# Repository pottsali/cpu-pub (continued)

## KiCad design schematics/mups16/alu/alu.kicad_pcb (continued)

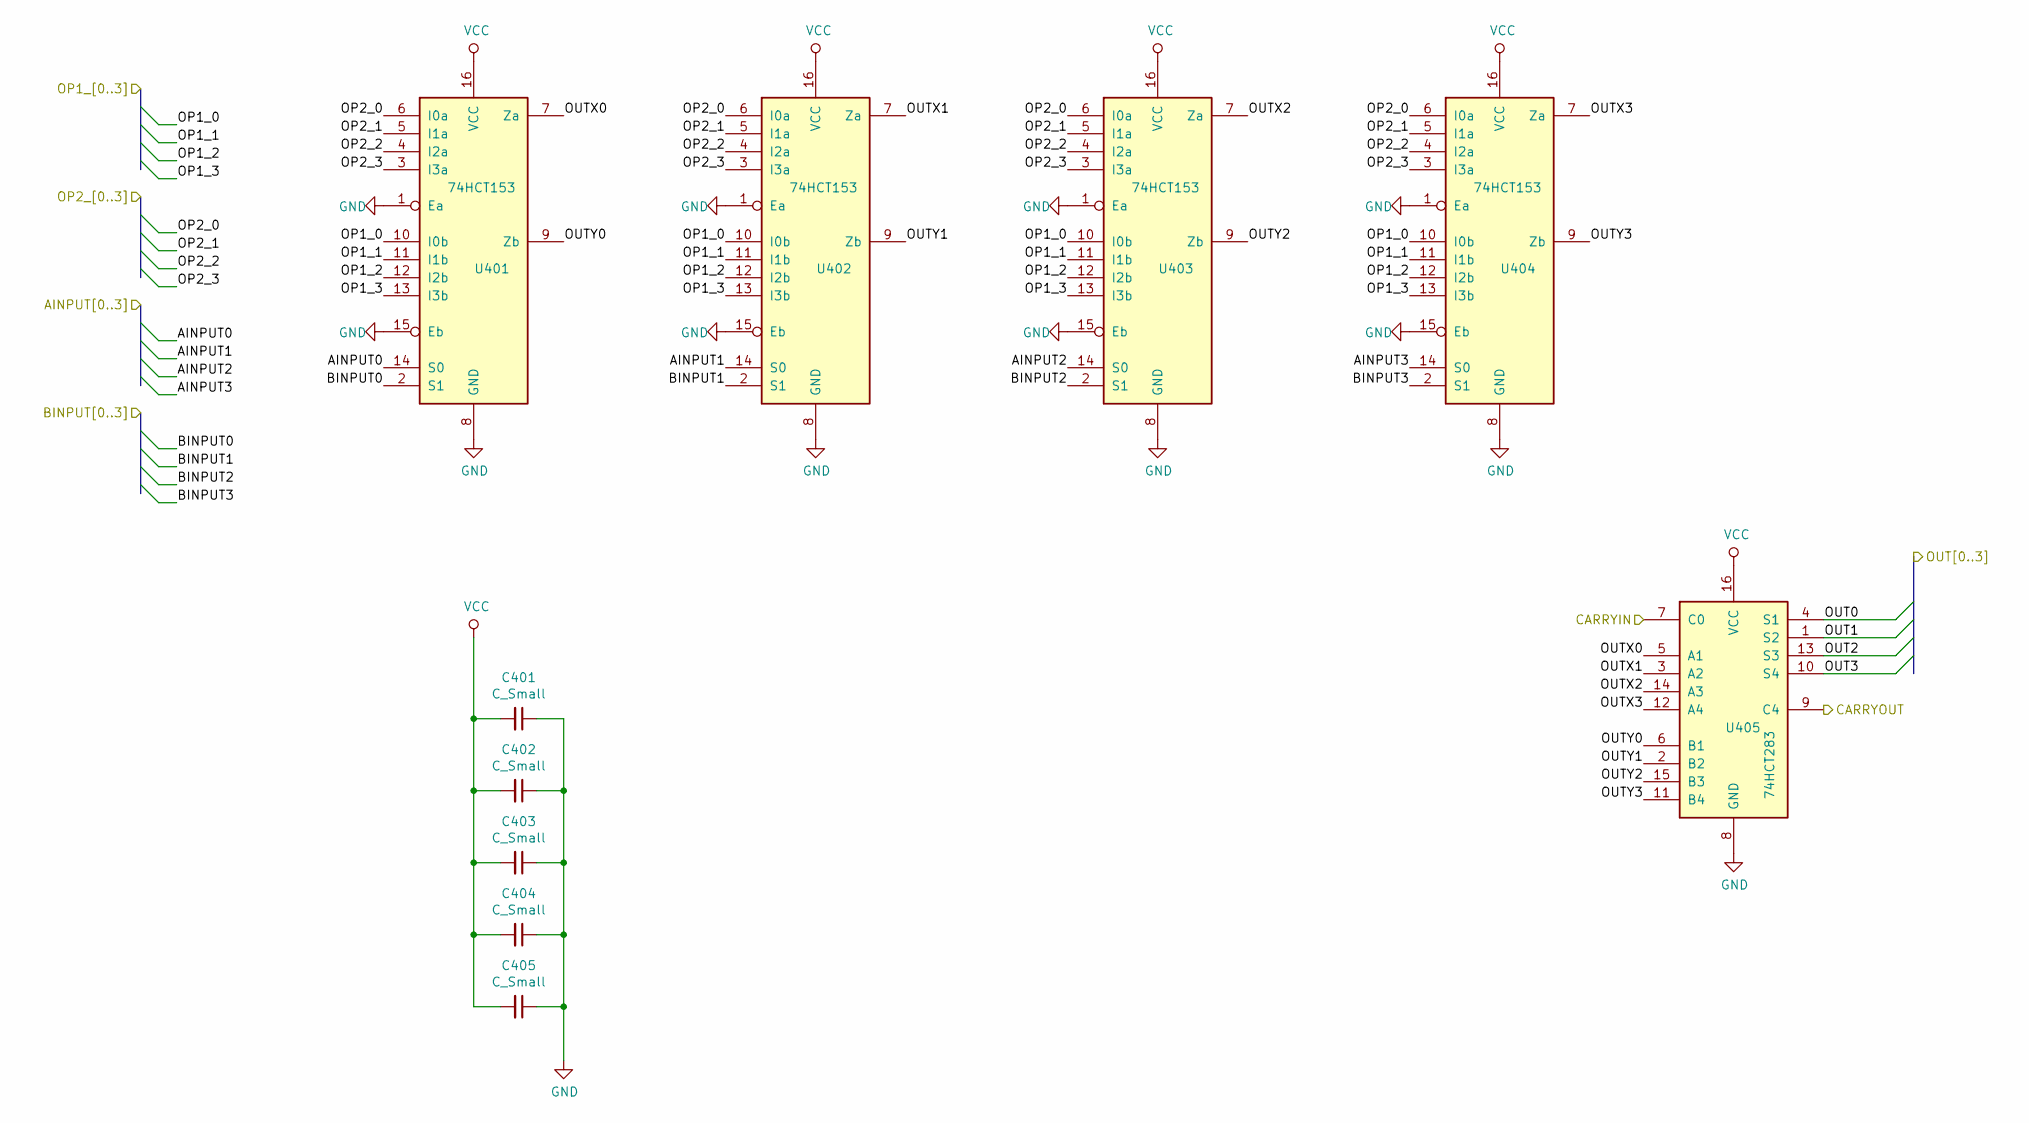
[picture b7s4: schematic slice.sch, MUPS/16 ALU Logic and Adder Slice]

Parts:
C401, C402, C403, C404, C405: C_Small; C_0805_2012Metric
U401, U402, U403, U404: 74HCT153; SOIC-16_3.9x9.9mm_P1.27mm
U405: 74HCT283; SOIC-16_3.9x9.9mm_P1.27mm

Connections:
/ADDOUT0: U405.4 (S1); also elsewhere on the board
/ADDOUT1: U405.1 (S2); also elsewhere on the board
/ADDOUT2: U405.13 (S3); also elsewhere on the board
/ADDOUT3: U405.10 (S4); also elsewhere on the board
/CARRYIN: U405.7 (C0); also elsewhere on the board
/OP_Y0: U401.10 (I0b), U402.10 (I0b), U403.10 (I0b), U404.10 (I0b); also elsewhere on the board
/OP_Y1: U401.11 (I1b), U402.11 (I1b), U403.11 (I1b), U404.11 (I1b); also elsewhere on the board
/OP_Y2: U401.12 (I2b), U402.12 (I2b), U403.12 (I2b), U404.12 (I2b); also elsewhere on the board
/OP_Y3: U401.13 (I3b), U402.13 (I3b), U403.13 (I3b), U404.13 (I3b); also elsewhere on the board
/slice0/OUTX0: U401.7 (Za), U405.5 (A1)
/slice0/OUTX1: U402.7 (Za), U405.3 (A2)
/slice0/OUTX2: U403.7 (Za), U405.14 (A3)
/slice0/OUTX3: U404.7 (Za), U405.12 (A4)
/slice0/OUTY0: U401.9 (Zb), U405.6 (B1)
/slice0/OUTY1: U402.9 (Zb), U405.2 (B2)
/slice0/OUTY2: U403.9 (Zb), U405.15 (B3)
/slice0/OUTY3: U404.9 (Zb), U405.11 (B4)
/slice1/CARRYIN: U405.9 (C4); also elsewhere on the board
BUSA0: U401.14 (S0); also elsewhere on the board
BUSA1: U402.14 (S0); also elsewhere on the board
BUSA2: U403.14 (S0); also elsewhere on the board
BUSA3: U404.14 (S0); also elsewhere on the board
BUSB0: U401.2 (S1); also elsewhere on the board
BUSB1: U402.2 (S1); also elsewhere on the board
BUSB2: U403.2 (S1); also elsewhere on the board
BUSB3: U404.2 (S1); also elsewhere on the board
GND: C401.1, C402.1, C403.1, C404.1, C405.1, U401.1 (Ea), U401.8 (GND), U401.15 (Eb), U402.1 (Ea), U402.8 (GND), U402.15 (Eb), U403.1 (Ea), U403.8 (GND), U403.15 (Eb), U404.1 (Ea), U404.8 (GND), U404.15 (Eb), U405.8 (GND); also elsewhere on the board
VCC: C401.2, C402.2, C403.2, C404.2, C405.2, U401.16 (VCC), U402.16 (VCC), U403.16 (VCC), U404.16 (VCC), U405.16 (VCC); also elsewhere on the board

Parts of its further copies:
C501, C502, C503, C504, C505, C601, C602, C603, C604, C605, C701, C702, C703, C704, C705: C_Small; C_0805_2012Metric
U501, U502, U503, U504, U601, U602, U603, U604, U701, U702, U703, U704: 74HCT153; SOIC-16_3.9x9.9mm_P1.27mm
U505, U605, U705: 74HCT283; SOIC-16_3.9x9.9mm_P1.27mm

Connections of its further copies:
/ADDOUT4: U505.4 (S1); also elsewhere on the board
/ADDOUT5: U505.1 (S2); also elsewhere on the board
/ADDOUT6: U505.13 (S3); also elsewhere on the board
/ADDOUT7: U505.10 (S4); also elsewhere on the board
/ADDOUT8: U605.4 (S1); also elsewhere on the board
/ADDOUT9: U605.1 (S2); also elsewhere on the board
/ADDOUT10: U605.13 (S3); also elsewhere on the board
/ADDOUT11: U605.10 (S4); also elsewhere on the board
/ADDOUT12: U705.4 (S1); also elsewhere on the board
/ADDOUT13: U705.1 (S2); also elsewhere on the board
/ADDOUT14: U705.13 (S3); also elsewhere on the board
/ADDOUT15: U705.10 (S4); also elsewhere on the board
/CARRYOUT: U705.9 (C4); also elsewhere on the board
/OP_Y0: U501.10 (I0b), U502.10 (I0b), U503.10 (I0b), U504.10 (I0b), U601.10 (I0b), U602.10 (I0b), U603.10 (I0b), U604.10 (I0b), U701.10 (I0b), U702.10 (I0b), U703.10 (I0b), U704.10 (I0b); also elsewhere on the board
/OP_Y1: U501.11 (I1b), U502.11 (I1b), U503.11 (I1b), U504.11 (I1b), U601.11 (I1b), U602.11 (I1b), U603.11 (I1b), U604.11 (I1b), U701.11 (I1b), U702.11 (I1b), U703.11 (I1b), U704.11 (I1b); also elsewhere on the board
/OP_Y2: U501.12 (I2b), U502.12 (I2b), U503.12 (I2b), U504.12 (I2b), U601.12 (I2b), U602.12 (I2b), U603.12 (I2b), U604.12 (I2b), U701.12 (I2b), U702.12 (I2b), U703.12 (I2b), U704.12 (I2b); also elsewhere on the board
/OP_Y3: U501.13 (I3b), U502.13 (I3b), U503.13 (I3b), U504.13 (I3b), U601.13 (I3b), U602.13 (I3b), U603.13 (I3b), U604.13 (I3b), U701.13 (I3b), U702.13 (I3b), U703.13 (I3b), U704.13 (I3b); also elsewhere on the board
/slice1/CARRYIN: U505.7 (C0); also elsewhere on the board
/slice1/OUTX0: U501.7 (Za), U505.5 (A1)
/slice1/OUTX1: U502.7 (Za), U505.3 (A2)
/slice1/OUTX2: U503.7 (Za), U505.14 (A3)
/slice1/OUTX3: U504.7 (Za), U505.12 (A4)
/slice1/OUTY0: U501.9 (Zb), U505.6 (B1)
/slice1/OUTY1: U502.9 (Zb), U505.2 (B2)
/slice1/OUTY2: U503.9 (Zb), U505.15 (B3)
/slice1/OUTY3: U504.9 (Zb), U505.11 (B4)
/slice2/CARRYIN: U505.9 (C4), U605.7 (C0)
/slice2/OUTX0: U601.7 (Za), U605.5 (A1)
/slice2/OUTX1: U602.7 (Za), U605.3 (A2)
/slice2/OUTX2: U603.7 (Za), U605.14 (A3)
/slice2/OUTX3: U604.7 (Za), U605.12 (A4)
/slice2/OUTY0: U601.9 (Zb), U605.6 (B1)
/slice2/OUTY1: U602.9 (Zb), U605.2 (B2)
/slice2/OUTY2: U603.9 (Zb), U605.15 (B3)
/slice2/OUTY3: U604.9 (Zb), U605.11 (B4)
/slice3/CARRYIN: U605.9 (C4), U705.7 (C0)
/slice3/OUTX0: U701.7 (Za), U705.5 (A1)
/slice3/OUTX1: U702.7 (Za), U705.3 (A2)
/slice3/OUTX2: U703.7 (Za), U705.14 (A3)
/slice3/OUTX3: U704.7 (Za), U705.12 (A4)
/slice3/OUTY0: U701.9 (Zb), U705.6 (B1)
/slice3/OUTY1: U702.9 (Zb), U705.2 (B2)
/slice3/OUTY2: U703.9 (Zb), U705.15 (B3)
/slice3/OUTY3: U704.9 (Zb), U705.11 (B4)
BUSA4: U501.14 (S0); also elsewhere on the board
BUSA5: U502.14 (S0); also elsewhere on the board
BUSA6: U503.14 (S0); also elsewhere on the board
BUSA7: U504.14 (S0); also elsewhere on the board
BUSA8: U601.14 (S0); also elsewhere on the board
BUSA9: U602.14 (S0); also elsewhere on the board
BUSA10: U603.14 (S0); also elsewhere on the board
BUSA11: U604.14 (S0); also elsewhere on the board
BUSA12: U701.14 (S0); also elsewhere on the board
BUSA13: U702.14 (S0); also elsewhere on the board
BUSA14: U703.14 (S0); also elsewhere on the board
BUSA15: U704.14 (S0); also elsewhere on the board
BUSB4: U501.2 (S1); also elsewhere on the board
BUSB5: U502.2 (S1); also elsewhere on the board
BUSB6: U503.2 (S1); also elsewhere on the board
BUSB7: U504.2 (S1); also elsewhere on the board
BUSB8: U601.2 (S1); also elsewhere on the board
BUSB9: U602.2 (S1); also elsewhere on the board
BUSB10: U603.2 (S1); also elsewhere on the board
BUSB11: U604.2 (S1); also elsewhere on the board
BUSB12: U701.2 (S1); also elsewhere on the board
BUSB13: U702.2 (S1); also elsewhere on the board
BUSB14: U703.2 (S1); also elsewhere on the board
BUSB15: U704.2 (S1); also elsewhere on the board
GND: C501.1, C502.1, C503.1, C504.1, C505.1, C601.1, C602.1, C603.1, C604.1, C605.1, C701.1, C702.1, C703.1, C704.1, C705.1, U501.1 (Ea), U501.8 (GND), U501.15 (Eb), U502.1 (Ea), U502.8 (GND), U502.15 (Eb), U503.1 (Ea), U503.8 (GND), U503.15 (Eb), U504.1 (Ea), U504.8 (GND), U504.15 (Eb), U505.8 (GND), U601.1 (Ea), U601.8 (GND), U601.15 (Eb), U602.1 (Ea), U602.8 (GND), U602.15 (Eb), U603.1 (Ea), U603.8 (GND), U603.15 (Eb), U604.1 (Ea), U604.8 (GND), U604.15 (Eb), U605.8 (GND), U701.1 (Ea), U701.8 (GND), U701.15 (Eb), U702.1 (Ea), U702.8 (GND), U702.15 (Eb), U703.1 (Ea), U703.8 (GND), U703.15 (Eb), U704.1 (Ea), U704.8 (GND), U704.15 (Eb), U705.8 (GND); also elsewhere on the board
VCC: C501.2, C502.2, C503.2, C504.2, C505.2, C601.2, C602.2, C603.2, C604.2, C605.2, C701.2, C702.2, C703.2, C704.2, C705.2, U501.16 (VCC), U502.16 (VCC), U503.16 (VCC), U504.16 (VCC), U505.16 (VCC), U601.16 (VCC), U602.16 (VCC), U603.16 (VCC), U604.16 (VCC), U605.16 (VCC), U701.16 (VCC), U702.16 (VCC), U703.16 (VCC), U704.16 (VCC), U705.16 (VCC); also elsewhere on the board

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
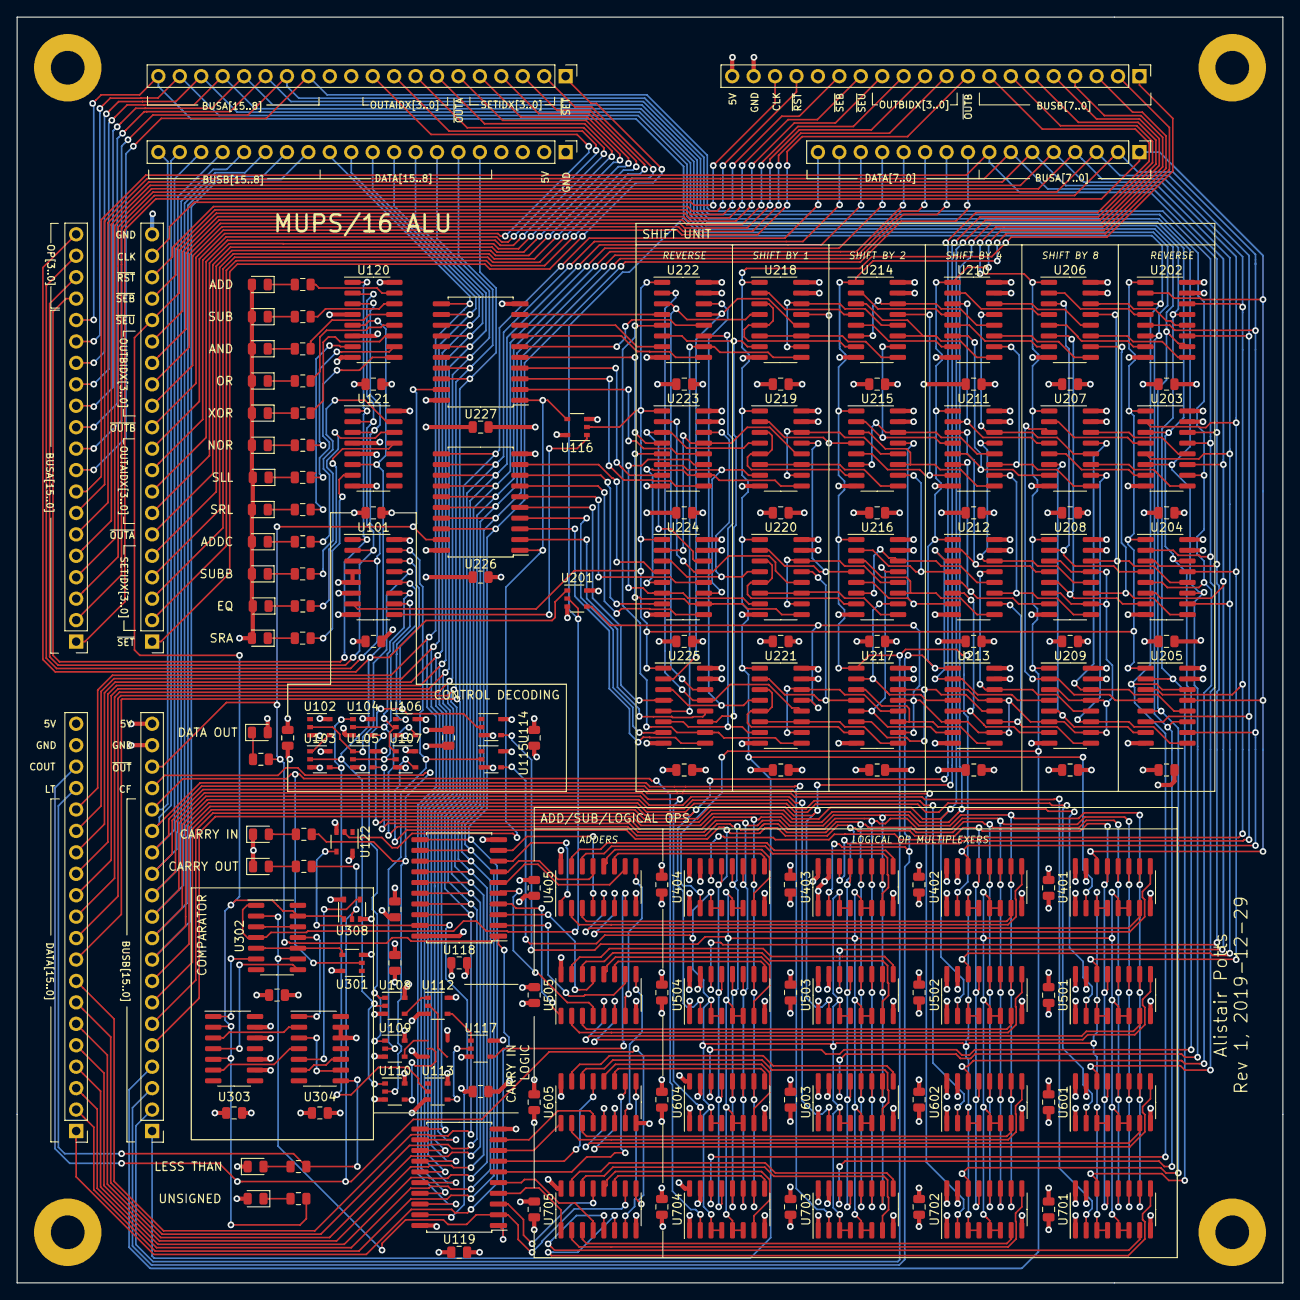
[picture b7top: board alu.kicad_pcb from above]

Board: 4 copper layers, 150.0 x 150.0 mm, 179 parts (0 on the bottom side), 286 nets.

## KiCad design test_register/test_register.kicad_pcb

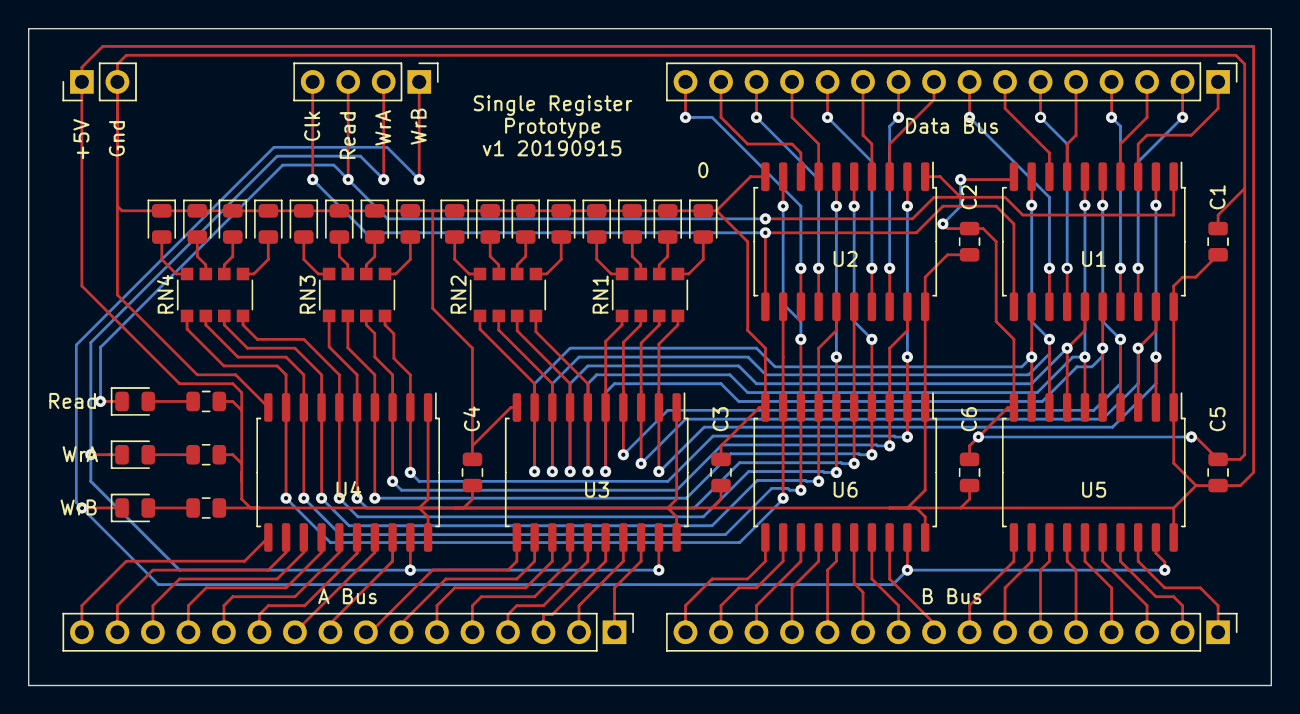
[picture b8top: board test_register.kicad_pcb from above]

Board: 2 copper layers, 88.9 x 47.0 mm, 43 parts (0 on the bottom side), 89 nets.

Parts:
0: LED; LED_0805_2012Metric
C1, C2, C3, C4, C5, C6: 100n; C_0805_2012Metric
D1: IN; LED_0805_2012Metric
D2: OUTA; LED_0805_2012Metric
D3: OUTB; LED_0805_2012Metric
D4, D5, D6, D8, D9, D10, D11, D12, D13, D14, D15, D16, D17, D18, D19: LED; LED_0805_2012Metric
J1: Data Bus; PinHeader_1x16_P2.54mm_Vertical
J2: Ctrl; PinHeader_1x04_P2.54mm_Vertical
J3: A Bus; PinHeader_1x16_P2.54mm_Vertical
J4: B Bus; PinHeader_1x16_P2.54mm_Vertical
J5: PWR; PinHeader_1x02_P2.54mm_Vertical
R1, R2, R3: 1K; R_0805_2012Metric
RN1, RN2, RN3, RN4: 1K; R_Array_Convex_4x1206
U1, U2: 74LS377; SOIC-20W_7.5x12.8mm_P1.27mm
U3, U4, U5, U6: 74LS245; SOIC-20W_7.5x12.8mm_P1.27mm

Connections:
/register/A0: J3.1, U3.18
/register/A1: J3.2, U3.17
/register/A2: J3.3, U3.16
/register/A3: J3.4, U3.15
/register/A4: J3.5, U3.14
/register/A5: J3.6, U3.13
/register/A6: J3.7, U3.12
/register/A7: J3.8, U3.11
/register/A8: J3.9, U4.18
/register/A9: J3.10, U4.17
/register/A10: J3.11, U4.16
/register/A11: J3.12, U4.15
/register/A12: J3.13, U4.14
/register/A13: J3.14, U4.13
/register/A14: J3.15, U4.12
/register/A15: J3.16, U4.11
/register/B0: J4.1, U5.18
/register/B1: J4.2, U5.17
/register/B2: J4.3, U5.16
/register/B3: J4.4, U5.15
/register/B4: J4.5, U5.14
/register/B5: J4.6, U5.13
/register/B6: J4.7, U5.12
/register/B7: J4.8, U5.11
/register/B8: J4.9, U6.18
/register/B9: J4.10, U6.17
/register/B10: J4.11, U6.16
/register/B11: J4.12, U6.15
/register/B12: J4.13, U6.14
/register/B13: J4.14, U6.13
/register/B14: J4.15, U6.12
/register/B15: J4.16, U6.11
/register/CLK: J2.4, U1.11, U2.11
/register/DATA0: J1.1, U1.3
/register/DATA1: J1.2, U1.18
/register/DATA2: J1.3, U1.4
/register/DATA3: J1.4, U1.17
/register/DATA4: J1.5, U1.7
/register/DATA5: J1.6, U1.14
/register/DATA6: J1.7, U1.8
/register/DATA7: J1.8, U1.13
/register/DATA8: J1.9, U2.3
/register/DATA9: J1.10, U2.18
/register/DATA10: J1.11, U2.4
/register/DATA11: J1.12, U2.17
/register/DATA12: J1.13, U2.7
/register/DATA13: J1.14, U2.14
/register/DATA14: J1.15, U2.8
/register/DATA15: J1.16, U2.13
/register/Q0: RN1.4, U1.2, U3.2, U5.2
/register/Q1: RN1.3, U1.19, U3.3, U5.3
/register/Q2: RN1.2, U1.5, U3.4, U5.4
/register/Q3: RN1.1, U1.16, U3.5, U5.5
/register/Q4: RN2.4, U1.6, U3.6, U5.6
/register/Q5: RN2.3, U1.15, U3.7, U5.7
/register/Q6: RN2.2, U1.9, U3.8, U5.8
/register/Q7: RN2.1, U1.12, U3.9, U5.9
/register/Q8: RN3.4, U2.2, U4.2, U6.2
/register/Q9: RN3.3, U2.19, U4.3, U6.3
/register/Q10: RN3.2, U2.5, U4.4, U6.4
/register/Q11: RN3.1, U2.16, U4.5, U6.5
/register/Q12: RN4.4, U2.6, U4.6, U6.6
/register/Q13: RN4.3, U2.15, U4.7, U6.7
/register/Q14: RN4.2, U2.9, U4.8, U6.8
/register/Q15: RN4.1, U2.12, U4.9, U6.9
/register/~IN: D1.1, J2.3, U1.1, U2.1
/register/~OUTA: D2.1, J2.2, U3.19, U4.19
/register/~OUTB: D3.1, J2.1, U5.19, U6.19
GND: 0.1, C1.1, C2.1, C3.1, C4.1, C5.1, C6.1, D4.1, D5.1, D6.1, D8.1, D9.1, D10.1, D11.1, D12.1, D13.1, D14.1, D15.1, D16.1, D17.1, D18.1, D19.1, J5.2, U1.10, U2.10, U3.10, U4.10, U5.10, U6.10
unnamed: D1.2, R1.2
unnamed: D2.2, R2.2
unnamed: D3.2, R3.2
unnamed: D4.2, RN1.8
unnamed: D5.2, RN1.7
unnamed: D6.2, RN1.6
unnamed: 0.2, RN1.5
unnamed: D8.2, RN2.8
unnamed: D9.2, RN2.7
unnamed: D10.2, RN2.6
unnamed: D11.2, RN2.5
unnamed: D12.2, RN3.8
unnamed: D13.2, RN3.7
unnamed: D14.2, RN3.6
unnamed: D15.2, RN3.5
unnamed: D16.2, RN4.8
unnamed: D17.2, RN4.7
unnamed: D18.2, RN4.6
unnamed: D19.2, RN4.5
VCC: C1.2, C2.2, C3.2, C4.2, C5.2, C6.2, J5.1, R1.1, R2.1, R3.1, U1.20, U2.20, U3.1, U3.20, U4.1, U4.20, U5.1, U5.20, U6.1, U6.20

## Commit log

2019-10-20 Initial commit containing test register
2020-07-01 Added schematics and PCBs for all components completed so far
